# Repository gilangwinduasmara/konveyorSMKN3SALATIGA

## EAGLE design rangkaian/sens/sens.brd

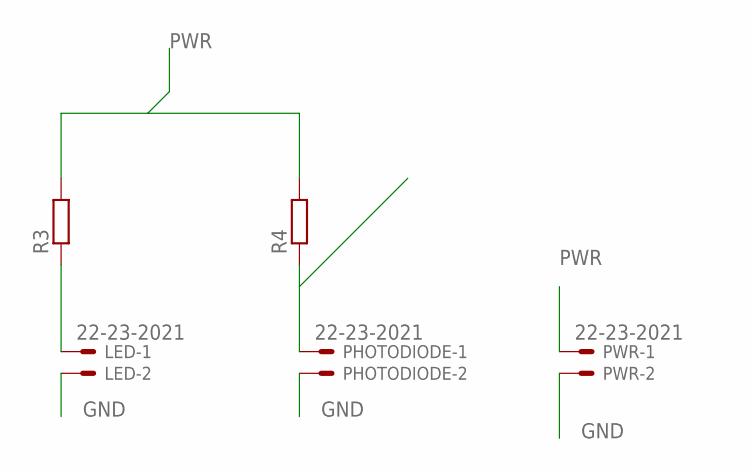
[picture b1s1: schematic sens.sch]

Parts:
LED: 22-23-2021
PHOTODIODE: 22-23-2021
PWR: 22-23-2021
R3, R4: R-EU_0207/7; 0207/7

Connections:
GND: LED.2, PHOTODIODE.2, PWR.2
unnamed: LED.1, R3.1
unnamed: PHOTODIODE.1, R4.1
PWR: PWR.1, R3.2, R4.2

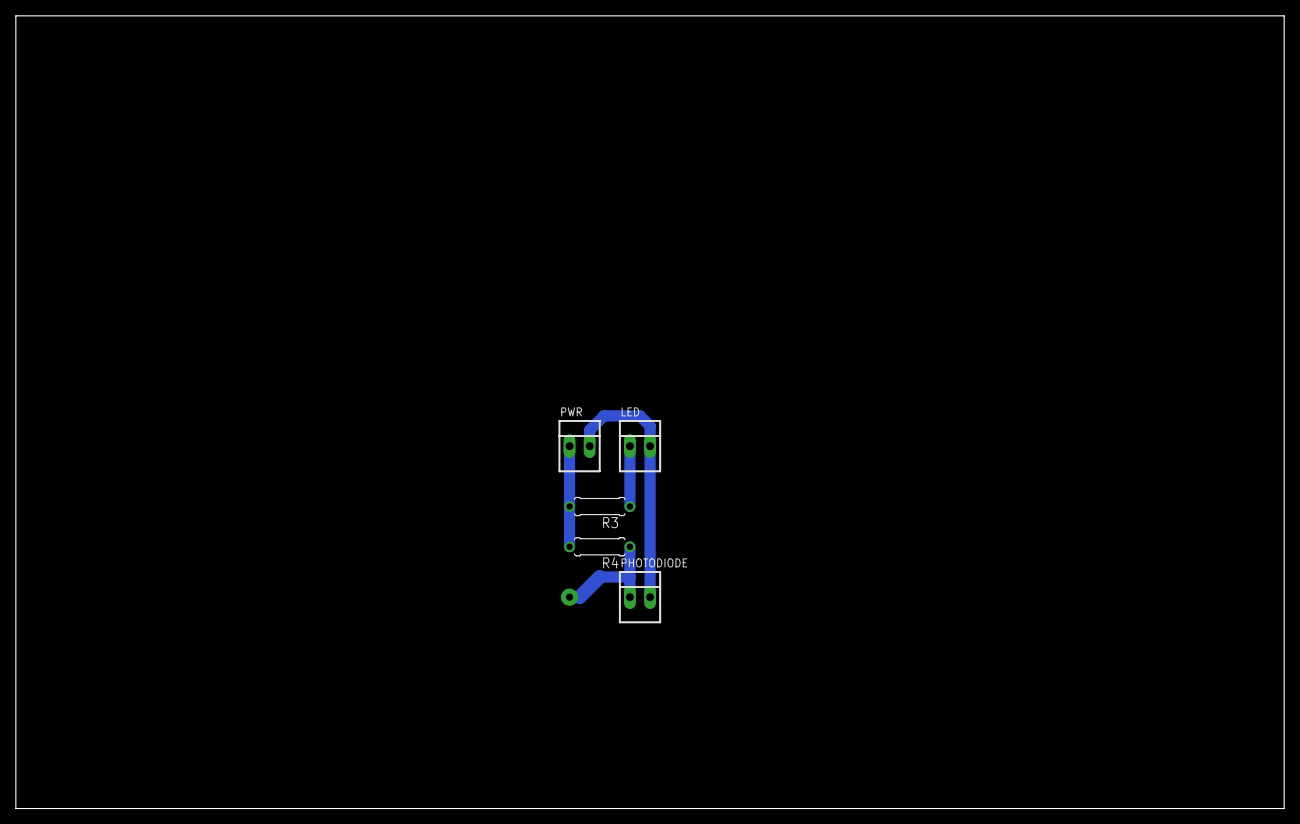
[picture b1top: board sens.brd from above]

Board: 2 copper layers, 160.0 x 100.0 mm, 5 parts (0 on the bottom side), 4 nets.

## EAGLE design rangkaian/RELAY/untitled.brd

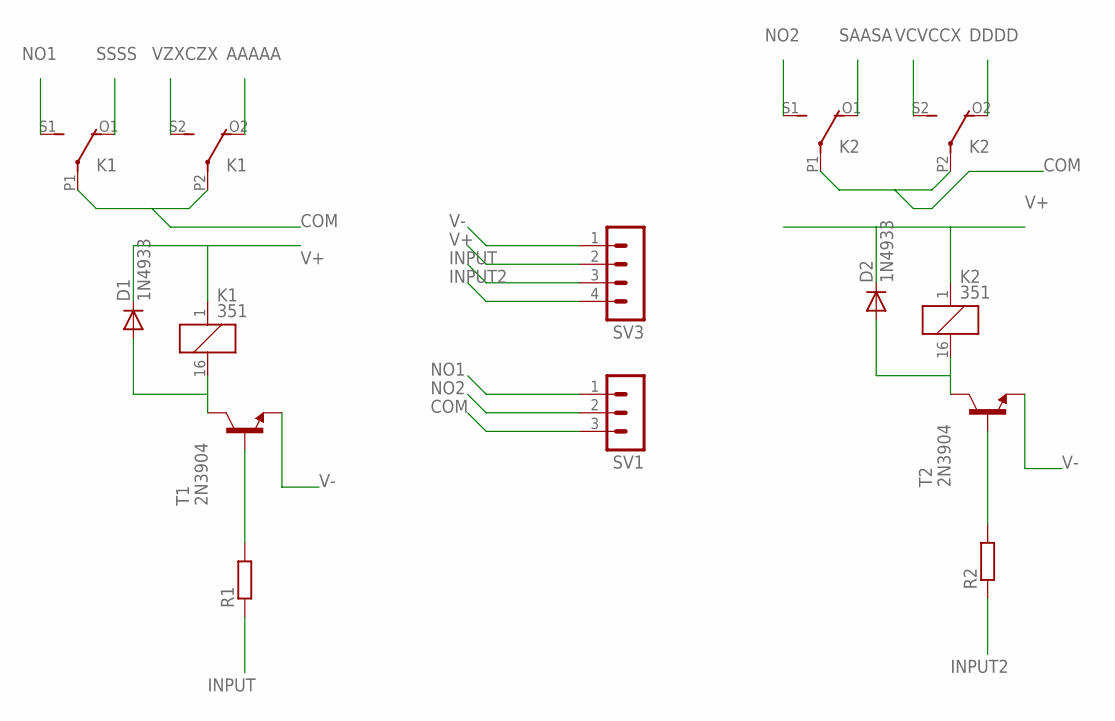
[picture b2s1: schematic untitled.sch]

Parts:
D1, D2: 1N4933; DO41-10
K1, K2: 351
R1, R2: R-EU_0309/12; 0309/12
SV1: MA03-1
SV3: MA04-1
T1, T2: 2N3904; TO92

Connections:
AAAAA: K1.O2 (O)
COM: K1.P1, K1.P2, K2.P1, K2.P2, SV1.3
DDDD: K2.O2 (O)
INPUT: R1.1, SV3.3
INPUT2: R2.1, SV3.4
unnamed: R1.2, T1.2 (B)
unnamed: R2.2, T2.2 (B)
unnamed: D2.A, K2.16 (2), T2.1 (C)
unnamed: D1.A, K1.16 (2), T1.1 (C)
NO1: K1.S1 (S), SV1.1
NO2: K2.S1 (S), SV1.2
SAASA: K2.O1 (O)
SSSS: K1.O1 (O)
V+: D1.C, D2.C, K1.1, K2.1, SV3.2
V-: SV3.1, T1.3 (E), T2.3 (E)
VCVCCX: K2.S2 (S)
VZXCZX: K1.S2 (S)

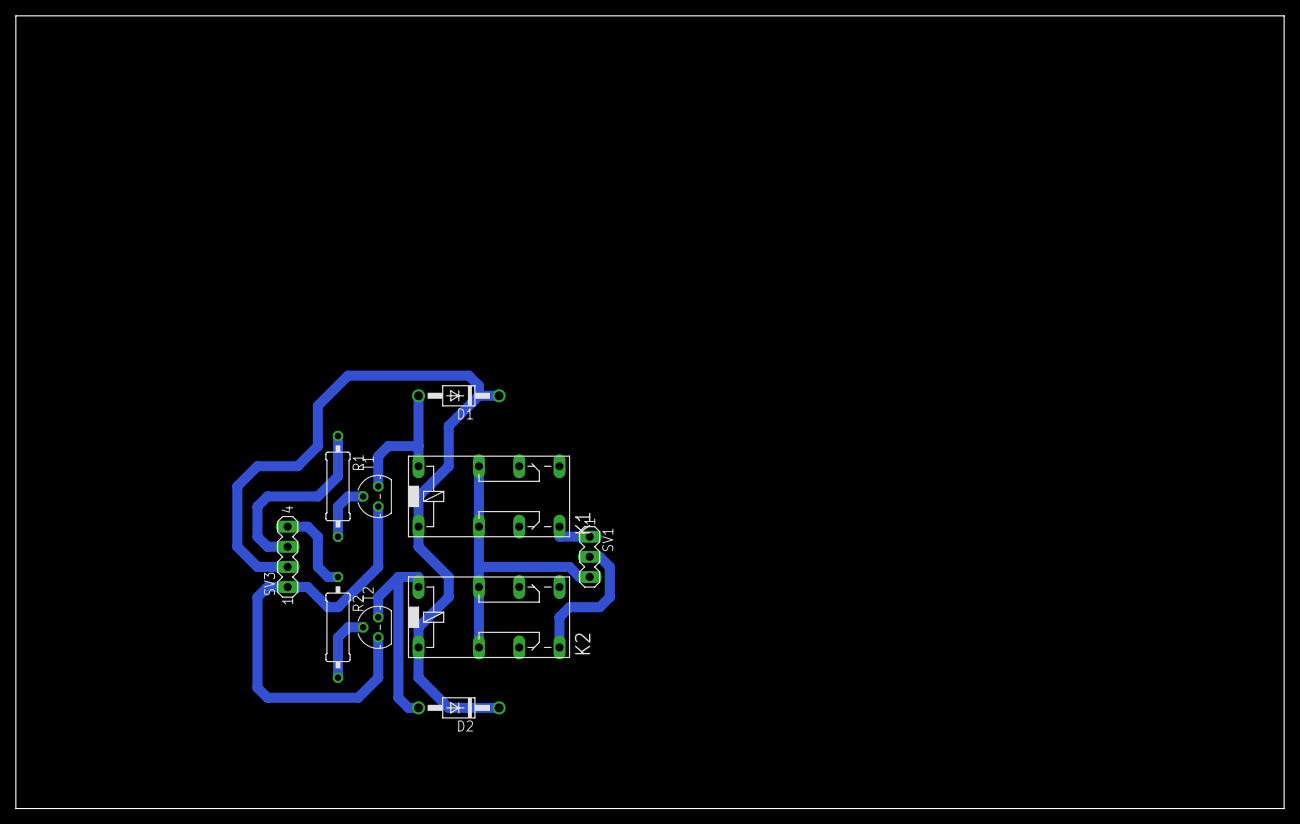
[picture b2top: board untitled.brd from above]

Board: 2 copper layers, 160.0 x 100.0 mm, 10 parts (0 on the bottom side), 11 nets.

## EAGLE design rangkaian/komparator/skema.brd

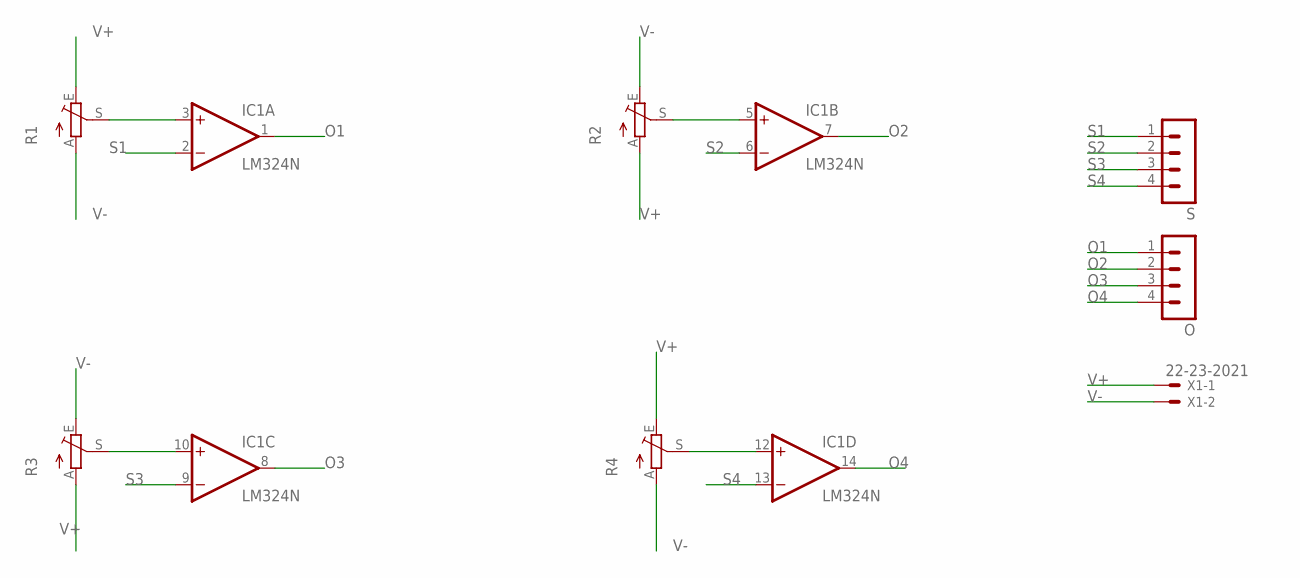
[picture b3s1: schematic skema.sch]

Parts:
IC1: LM324N; DIL14
O: MA04-1
R1, R2, R3, R4: TRIM_EU-CA6V; CA6V
S: MA04-1
X1: 22-23-2021

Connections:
unnamed: IC1.3 (+IN), R1.S
unnamed: IC1.10 (+IN), R3.S
unnamed: IC1.5 (+IN), R2.S
unnamed: IC1.12 (+IN), R4.S
O1: IC1.1 (OUT), O.1
O2: IC1.7 (OUT), O.2
O3: IC1.8 (OUT), O.3
O4: IC1.14 (OUT), O.4
S1: IC1.2 (-IN), S.1
S2: IC1.6 (-IN), S.2
S3: IC1.9 (-IN), S.3
S4: IC1.13 (-IN), S.4
V+: IC1.4 (V+), R1.E, R2.A, R3.A, R4.E, X1.1
V-: IC1.11 (V-), R1.A, R2.E, R3.E, R4.A, X1.2

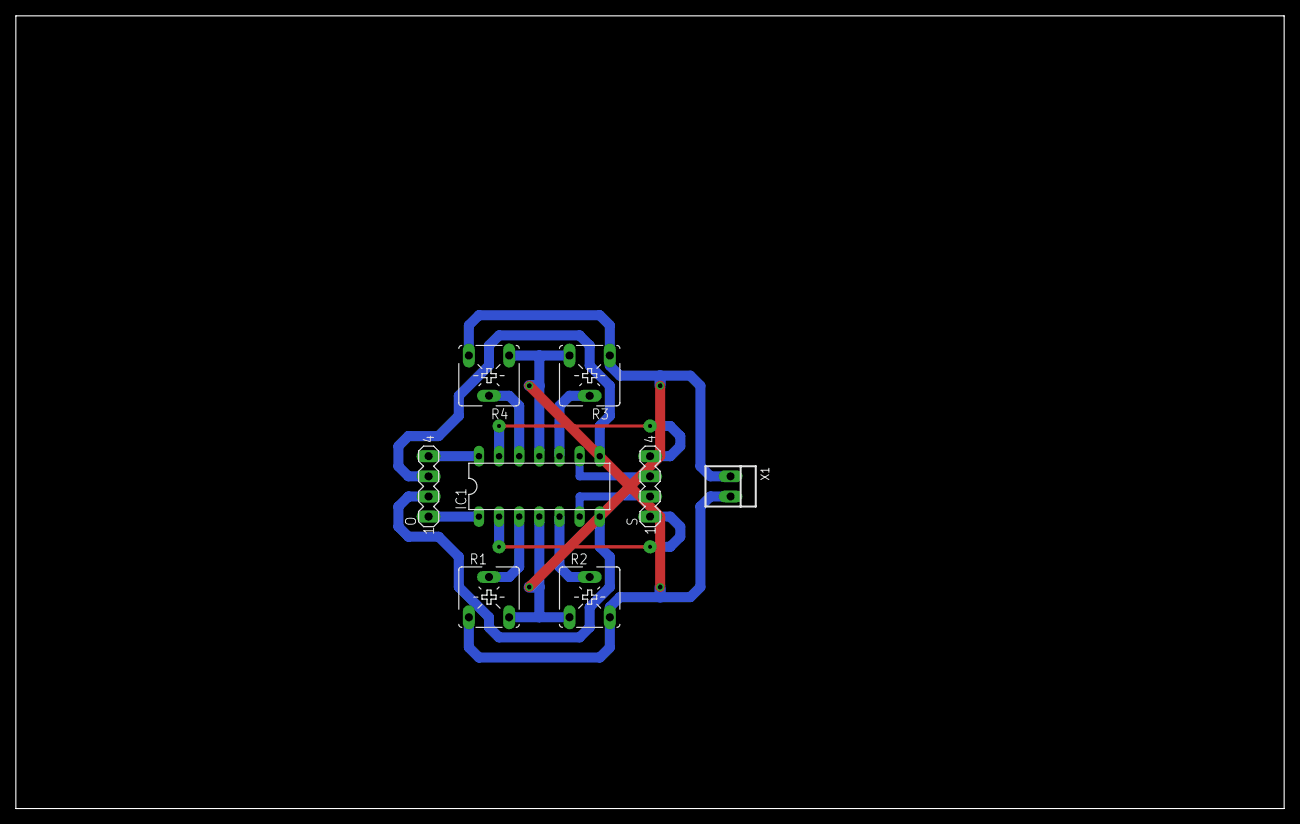
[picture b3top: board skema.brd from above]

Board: 2 copper layers, 160.0 x 100.0 mm, 8 parts (0 on the bottom side), 14 nets.

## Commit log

2017-09-10 menambahkan desain rangkaian
2017-09-10 menambahkan SourceCode
